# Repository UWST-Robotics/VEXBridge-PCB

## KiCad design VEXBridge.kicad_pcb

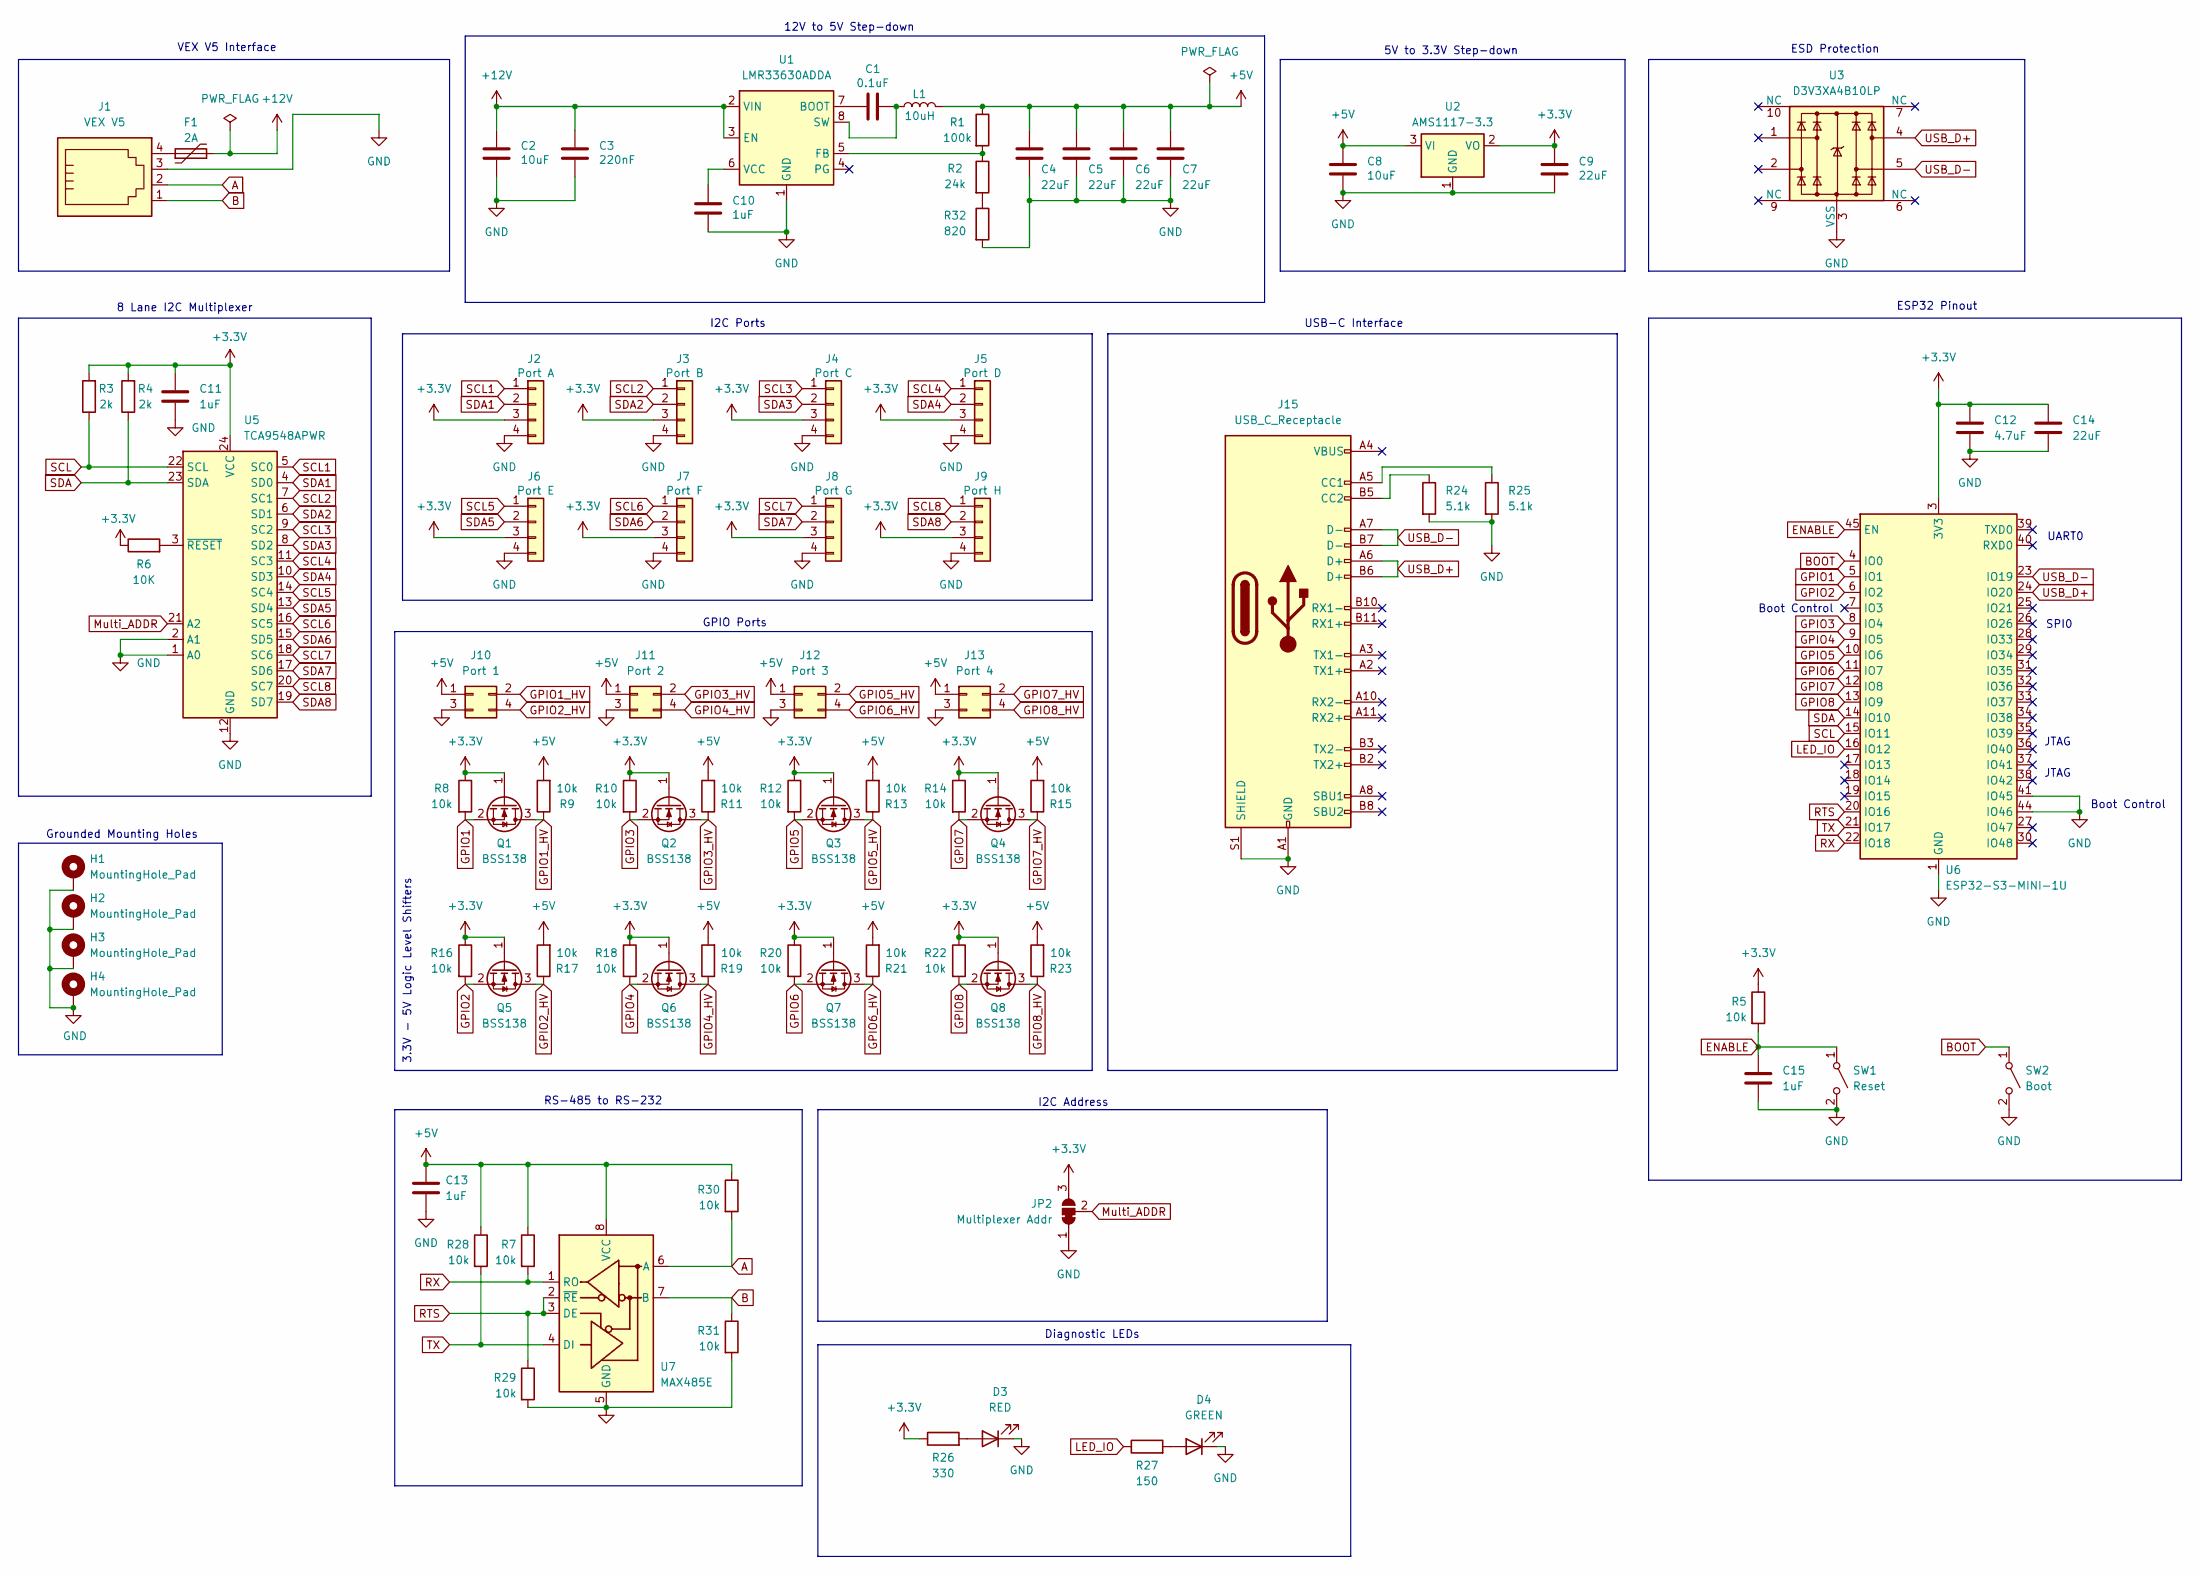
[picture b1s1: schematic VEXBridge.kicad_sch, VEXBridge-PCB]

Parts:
C1: 0.1uF; C_0603_1608Metric
C2, C8: 10uF; C_0603_1608Metric
C3: 220nF; C_0402_1005Metric
C4, C5, C6, C7, C9, C14: 22uF; C_0805_2012Metric
C10, C11, C13, C15: 1uF; C_0603_1608Metric
C12: 4.7uF; C_0603_1608Metric
D3: RED; LED_0603_1608Metric
D4: GREEN; LED_0603_1608Metric
F1: 2A; Fuse_1812_4532Metric
H1, H2, H3, H4: MountingHole_Pad; MountingHole_2.7mm_M2.5_Pad
J1: VEX V5; RJ9_Evercom_5301-440xxx_Horizontal
J2: Port A; JST_SH_SM04B-SRSS-TB_1x04-1MP_P1.00mm_Horizontal
J3: Port B; JST_SH_SM04B-SRSS-TB_1x04-1MP_P1.00mm_Horizontal
J4: Port C; JST_SH_SM04B-SRSS-TB_1x04-1MP_P1.00mm_Horizontal
J5: Port D; JST_SH_SM04B-SRSS-TB_1x04-1MP_P1.00mm_Horizontal
J6: Port E; JST_SH_SM04B-SRSS-TB_1x04-1MP_P1.00mm_Horizontal
J7: Port F; JST_SH_SM04B-SRSS-TB_1x04-1MP_P1.00mm_Horizontal
J8: Port G; JST_SH_SM04B-SRSS-TB_1x04-1MP_P1.00mm_Horizontal
J9: Port H; JST_SH_SM04B-SRSS-TB_1x04-1MP_P1.00mm_Horizontal
J10: Port 1; Molex_Mini-Fit_Jr_5569-04A2_2x02_P4.20mm_Horizontal
J11: Port 2; Molex_Mini-Fit_Jr_5569-04A2_2x02_P4.20mm_Horizontal
J12: Port 3; Molex_Mini-Fit_Jr_5569-04A2_2x02_P4.20mm_Horizontal
J13: Port 4; Molex_Mini-Fit_Jr_5569-04A2_2x02_P4.20mm_Horizontal
J15: USB_C_Receptacle; USB_C_Receptacle_Molex_105450-0101
JP2: Multiplexer Addr; SolderJumper-3_P1.3mm_Bridged12_RoundedPad1.0x1.5mm
L1: 10uH; L_TechFuse_SL0420
Q1, Q2, Q3, Q4, Q5, Q6, Q7, Q8: BSS138; SOT-23-3
R1: 100k; R_0805_2012Metric
R2: 24k; R_0805_2012Metric
R3, R4: 2k; R_0805_2012Metric
R5, R7, R8, R9, R10, R11, R12, R13, R14, R15, R16, R17, R18, R19, R20, R21, R22, R23, R28, R29, R30, R31: 10k; R_0805_2012Metric
R6: 10K; R_0805_2012Metric
R24, R25: 5.1k; R_0805_2012Metric
R26: 330; R_0805_2012Metric
R27: 150; R_0805_2012Metric
R32: 820; R_0603_1608Metric
SW1: Reset; SW_SPST_TS-1088-xR020
SW2: Boot; SW_SPST_TS-1088-xR020
U1: LMR33630ADDA; Texas_HSOP-8-1EP_3.9x4.9mm_P1.27mm_ThermalVias
U2: AMS1117-3.3; SOT-223-3_TabPin2
U3: D3V3XA4B10LP; Diodes_UDFN-10_1x2.5mm_P0.5mm
U5: TCA9548APWR; TSSOP-24_4.4x7.8mm_P0.65mm
U6: ESP32-S3-MINI-1U; ESP32-S2-MINI-1U
U7: MAX485E; SOIC-8_3.9x4.9mm_P1.27mm

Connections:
+3.3V: C9.1, C11.1, C12.1, C14.1, J2.3, J3.3, J4.3, J5.3, J6.3, J7.3, J8.3, J9.3, JP2.3 (B), Q1.1 (G), Q2.1 (G), Q3.1 (G), Q4.1 (G), Q5.1 (G), Q6.1 (G), Q7.1 (G), Q8.1 (G), R3.2, R4.2, R5.1, R6.1, R8.1, R10.1, R12.1, R14.1, R16.1, R18.1, R20.1, R22.1, R26.1, U2.2 (VO), U5.24 (VCC), U6.3 (3V3)
+5V: C4.1, C5.1, C6.1, C7.1, C8.1, C13.1, J10.1, J11.1, J12.1, J13.1, L1.2, R1.1, R7.1, R9.2, R11.2, R13.2, R15.2, R17.2, R19.2, R21.2, R23.2, R28.1, R30.1, U2.3 (VI), U7.8 (VCC)
+12V: C2.1, C3.1, F1.2, U1.2 (VIN), U1.3 (EN)
A: J1.2, R30.2, U7.6 (A)
B: J1.1, R31.1, U7.7 (B)
BOOT: SW2.1 (A), U6.4 (IO0)
ENABLE: C15.1, R5.2, SW1.1 (A), U6.45 (EN)
GND: C2.2, C3.2, C4.2, C5.2, C6.2, C7.2, C8.2, C9.2, C10.2, C11.2, C12.2, C13.2, C14.2, C15.2, D3.1 (K), D4.1 (K), H1.1 (1_1), H2.1 (1_1), H3.1 (1_1), H4.1 (1_1), J1.3, J2.4, J3.4, J4.4, J5.4, J6.4, J7.4, J8.4, J9.4, J10.3, J11.3, J12.3, J13.3, J15.A1 (GND_A1), J15.A12 (GND_A12), J15.B1 (GND_B1), J15.B12 (GND_B12), J15.S1 (SHIELD), J15.SH (SHIELD_S1), JP2.1 (A), R24.2, R25.2, R29.2, R31.2, R32.2, SW1.2 (B), SW2.2 (B), U1.1 (GND), U1.9 (GND), U2.1 (GND), U3.3 (VSS), U3.8 (VSS), U5.1 (A0), U5.2 (A1), U5.12 (GND), U6.1 (GND), U6.2 (GND), U6.41 (IO45), U6.42 (GND), U6.43 (GND), U6.44 (IO46), U6.46 (GND), U6.47 (GND), U6.48 (GND), U6.49 (GND), U6.50 (GND), U6.51 (GND), U6.52 (GND), U6.53 (GND), U6.54 (GND), U6.55 (GND), U6.56 (GND), U6.57 (GND), U6.58 (GND), U6.59 (GND), U6.60 (GND), U6.61 (GND), U6.62 (GND), U6.63 (GND), U6.64 (GND), U6.65 (GND), U7.5 (GND)
GPIO1: Q1.2 (S), R8.2, U6.5 (IO1)
GPIO1_HV: J10.2, Q1.3 (D), R9.1
GPIO2: Q5.2 (S), R16.2, U6.6 (IO2)
GPIO2_HV: J10.4, Q5.3 (D), R17.1
GPIO3: Q2.2 (S), R10.2, U6.8 (IO4)
GPIO3_HV: J11.2, Q2.3 (D), R11.1
GPIO4: Q6.2 (S), R18.2, U6.9 (IO5)
GPIO4_HV: J11.4, Q6.3 (D), R19.1
GPIO5: Q3.2 (S), R12.2, U6.10 (IO6)
GPIO5_HV: J12.2, Q3.3 (D), R13.1
GPIO6: Q7.2 (S), R20.2, U6.11 (IO7)
GPIO6_HV: J12.4, Q7.3 (D), R21.1
GPIO7: Q4.2 (S), R14.2, U6.12 (IO8)
GPIO7_HV: J13.2, Q4.3 (D), R15.1
GPIO8: Q8.2 (S), R22.2, U6.13 (IO9)
GPIO8_HV: J13.4, Q8.3 (D), R23.1
LED_IO: R27.1, U6.16 (IO12)
Multi_ADDR: JP2.2 (C), U5.21 (A2)
unnamed: D3.2 (A), R26.2
unnamed: D4.2 (A), R27.2
unnamed: F1.1, J1.4
unnamed: J15.A5 (CC1_A5), R25.1
unnamed: J15.B5 (CC2_B5), R24.1
unnamed: R2.2, R32.1
unnamed: C1.1, U1.7 (BOOT)
unnamed: R1.2, R2.1, U1.5 (FB)
unnamed: C1.2, L1.1, U1.8 (SW)
unnamed: C10.1, U1.6 (VCC)
unnamed: R6.2, U5.3 (~RESET)
RTS: R29.1, U6.20 (IO16), U7.2 (~RE), U7.3 (DE)
RX: R7.2, U6.22 (IO18), U7.1 (RO)
SCL: R3.1, U5.22 (SCL), U6.15 (IO11)
SCL1: J2.1, U5.5 (SC0)
SCL2: J3.1, U5.7 (SC1)
SCL3: J4.1, U5.9 (SC2)
SCL4: J5.1, U5.11 (SC3)
SCL5: J6.1, U5.14 (SC4)
SCL6: J7.1, U5.16 (SC5)
SCL7: J8.1, U5.18 (SC6)
SCL8: J9.1, U5.20 (SC7)
SDA: R4.1, U5.23 (SDA), U6.14 (IO10)
SDA1: J2.2, U5.4 (SD0)
SDA2: J3.2, U5.6 (SD1)
SDA3: J4.2, U5.8 (SD2)
SDA4: J5.2, U5.10 (SD3)
SDA5: J6.2, U5.13 (SD4)
SDA6: J7.2, U5.15 (SD5)
SDA7: J8.2, U5.17 (SD6)
SDA8: J9.2, U5.19 (SD7)
TX: R28.2, U6.21 (IO17), U7.4 (DI)
USB_D+: J15.A6 (D+_A6), J15.B6 (D+_B6), U3.4, U6.24 (IO20)
USB_D-: J15.A7 (D-_A7), J15.B7 (D-_B7), U3.5, U6.23 (IO19)

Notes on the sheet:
GPIO Ports
ESD Protection
SPI0
8 Lane I2C Multiplexer
3.3V - 5V Logic Level Shifters
I2C Address
USB-C Interface
JTAG
VEX V5 Interface
RS-485 to RS-232
Diagnostic LEDs
Boot Control
ESP32 Pinout
5V to 3.3V Step-down
UART0
Grounded Mounting Holes
I2C Ports
12V to 5V Step-down

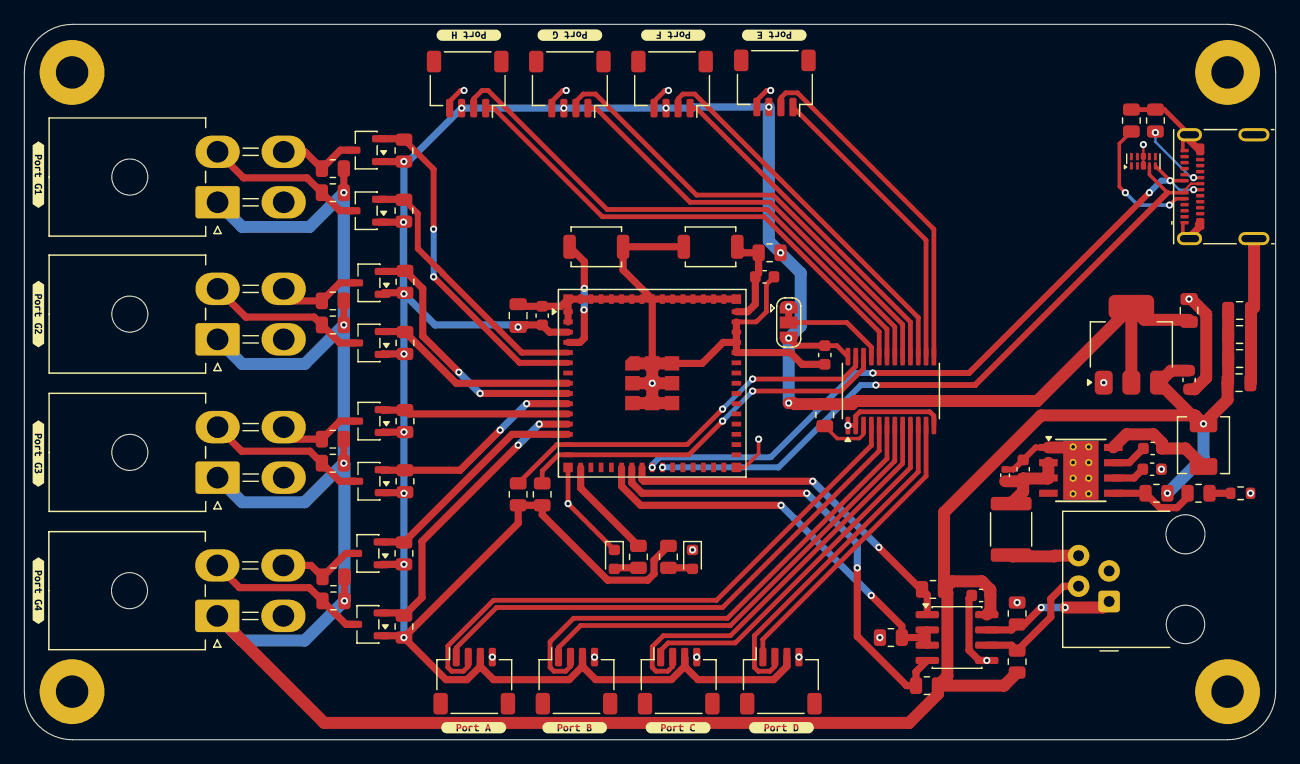
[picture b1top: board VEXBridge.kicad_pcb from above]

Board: 2 copper layers, 104.1 x 59.5 mm, 98 parts (0 on the bottom side), 60 nets.

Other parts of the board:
kibuzzard-69FA45C9: G***; kibuzzard-69FA45C9
kibuzzard-69FA46AE: G***; kibuzzard-69FA46AE
kibuzzard-69FA46BE: G***; kibuzzard-69FA46BE
kibuzzard-69FA46C2: G***; kibuzzard-69FA46C2
kibuzzard-69FA46C9: G***; kibuzzard-69FA46C9
kibuzzard-69FA461D: G***; kibuzzard-69FA461D
kibuzzard-69FA465C: G***; kibuzzard-69FA465C
kibuzzard-69FA4619: G***; kibuzzard-69FA4619
kibuzzard-69FA4621: G***; kibuzzard-69FA4621
kibuzzard-69FA4660: G***; kibuzzard-69FA4660
kibuzzard-69FA4664: G***; kibuzzard-69FA4664
kibuzzard-69FA4669: G***; kibuzzard-69FA4669

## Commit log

2025-10-28 VEXBridge v2 (WIP)
2025-10-29 Added a 8 bit multiplexer
2025-11-07 Bug Fixes for PCB Draft
    - Replaced LEDs with a single RGB LED
    - Routed 4 QWIIC connectors directly to ESP32 instead of multiplexer
    - Replaced IMU and added IMU address jumper
2025-12-03 I have no idea what I did
2026-03-22 Completed schematic
2026-03-25 Initial PCB Design w/o power rails
2026-03-28 (Mostly) complete PCB routing
2026-05-13 Near-Final PCB Design
2026-05-24 Fixed USB-C via diameters
2026-05-24 Added JLCPCB Order Files
